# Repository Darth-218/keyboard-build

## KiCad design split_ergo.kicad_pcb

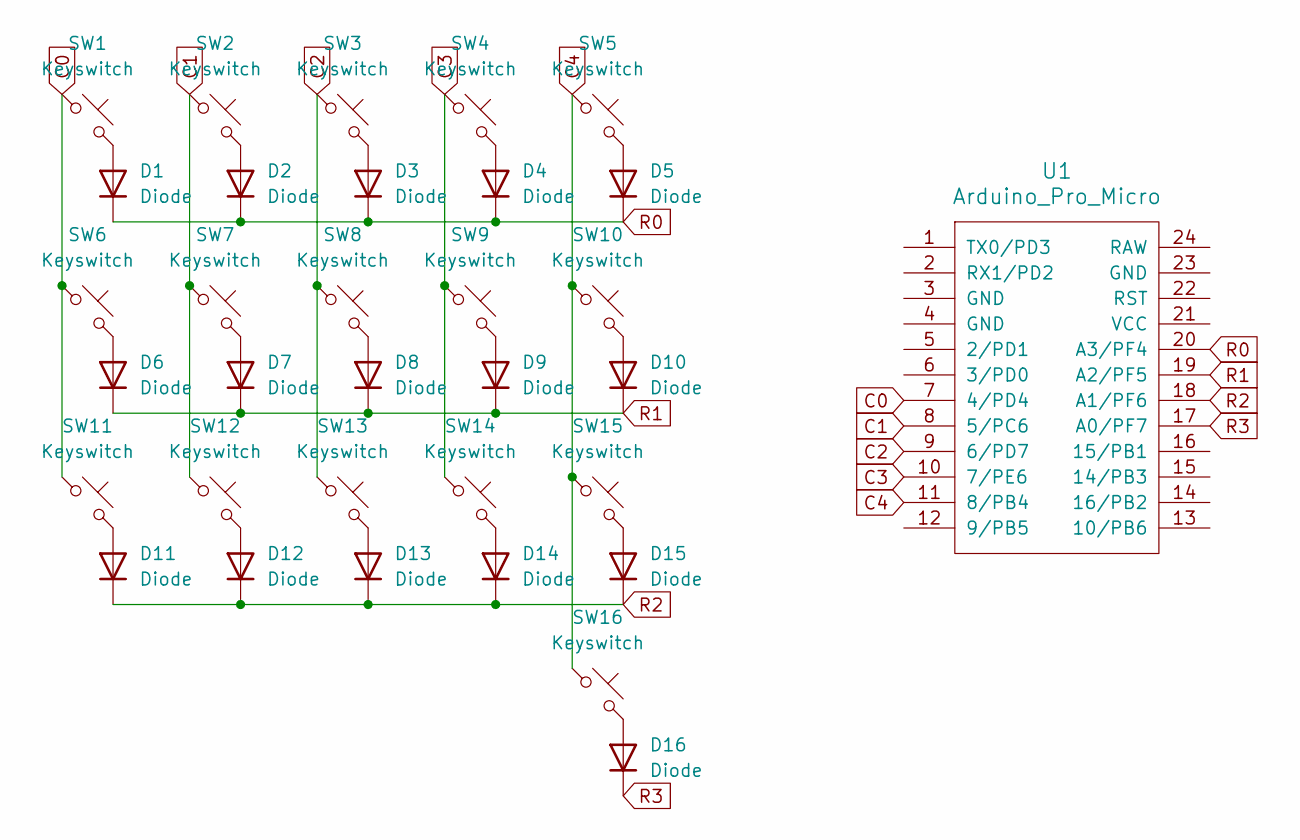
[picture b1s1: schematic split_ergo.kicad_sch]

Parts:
D1, D2, D3, D4, D5, D6, D7, D8, D9, D10, D11, D12, D13, D14, D15, D16: Diode; D_DO-35_SOD27_P7.62mm_Horizontal
SW1, SW2, SW3, SW4, SW5, SW6, SW7, SW8, SW9, SW10, SW11, SW12, SW13, SW14, SW15, SW16: Keyswitch; MX_PCB_1.00u
U1: Arduino_Pro_Micro

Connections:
C0: SW1.1, SW6.1, SW11.1, U1.7 (4/PD4)
C1: SW2.1, SW7.1, SW12.1, U1.8 (5/PC6)
C2: SW3.1, SW8.1, SW13.1, U1.9 (6/PD7)
C3: SW4.1, SW9.1, SW14.1, U1.10 (7/PE6)
C4: SW5.1, SW10.1, SW15.1, SW16.1, U1.11 (8/PB4)
unnamed: D1.2 (A), SW1.2
unnamed: D2.2 (A), SW2.2
unnamed: D3.2 (A), SW3.2
unnamed: D4.2 (A), SW4.2
unnamed: D5.2 (A), SW5.2
unnamed: D6.2 (A), SW6.2
unnamed: D7.2 (A), SW7.2
unnamed: D8.2 (A), SW8.2
unnamed: D9.2 (A), SW9.2
unnamed: D10.2 (A), SW10.2
unnamed: D11.2 (A), SW11.2
unnamed: D12.2 (A), SW12.2
unnamed: D13.2 (A), SW13.2
unnamed: D14.2 (A), SW14.2
unnamed: D15.2 (A), SW15.2
unnamed: D16.2 (A), SW16.2
R0: D1.1 (K), D2.1 (K), D3.1 (K), D4.1 (K), D5.1 (K), U1.20 (A3/PF4)
R1: D6.1 (K), D7.1 (K), D8.1 (K), D9.1 (K), D10.1 (K), U1.19 (A2/PF5)
R2: D11.1 (K), D12.1 (K), D13.1 (K), D14.1 (K), D15.1 (K), U1.18 (A1/PF6)
R3: D16.1 (K), U1.17 (A0/PF7)

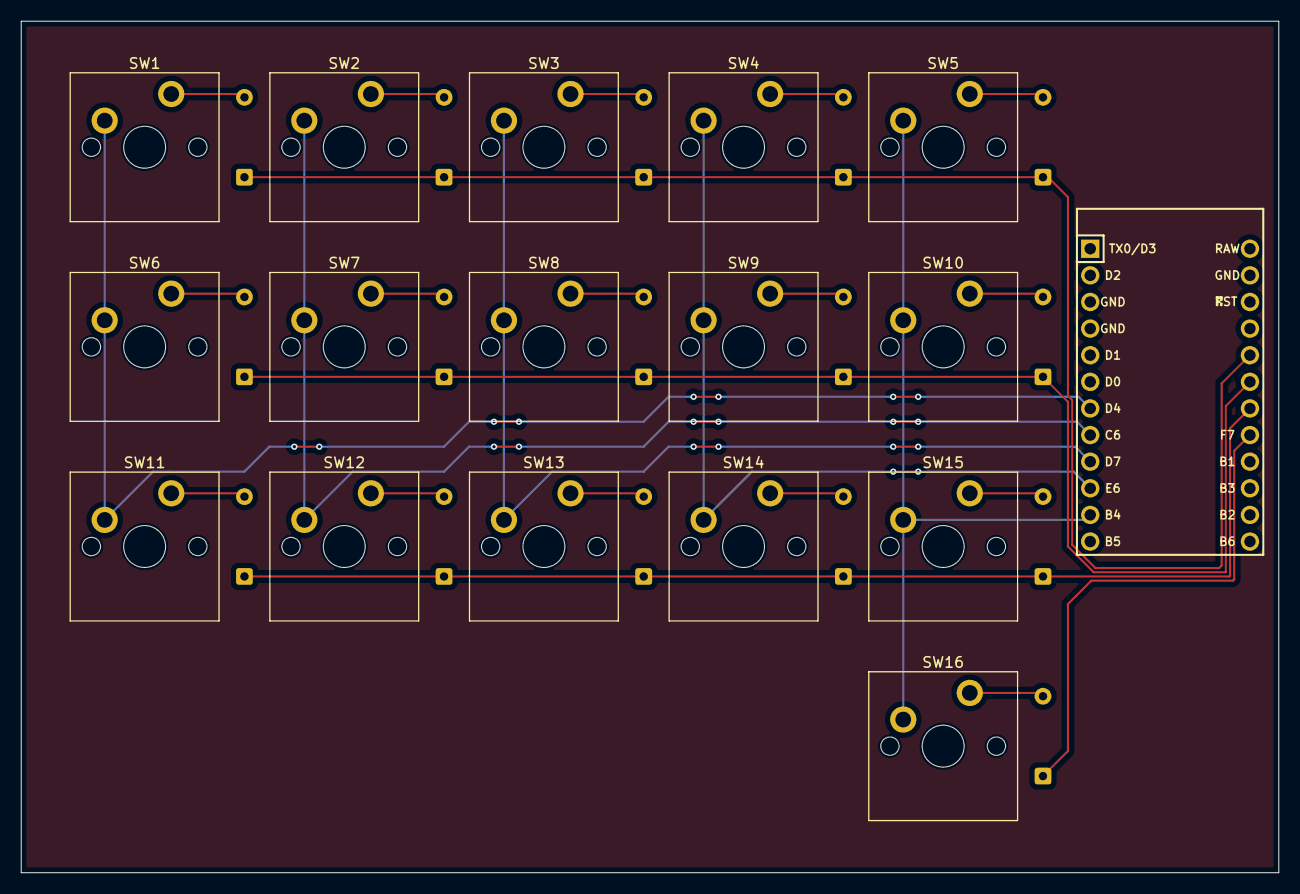
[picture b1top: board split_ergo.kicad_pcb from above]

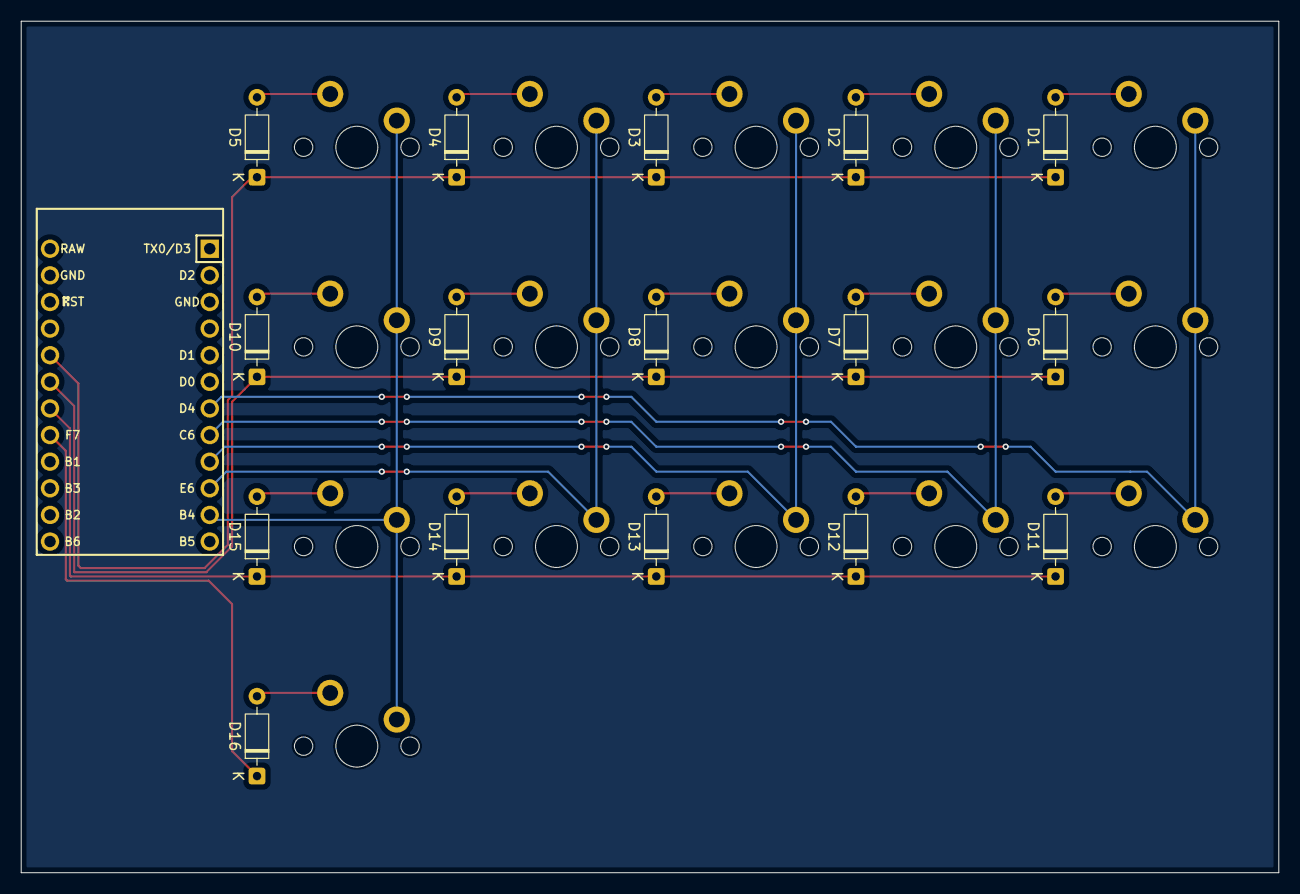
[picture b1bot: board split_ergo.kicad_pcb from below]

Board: 2 copper layers, 120.0 x 81.2 mm, 33 parts (16 on the bottom side), 25 nets.
